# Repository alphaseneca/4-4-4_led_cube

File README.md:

# 4x4x4 LED Cube Project

This repository documents my journey of building a **4x4x4 LED Cube**, including the code, PCB designs, mistakes I made, lessons learned and resources I found along the way. The goal is to use this repository as a **learning journal** and a **reference** for others. This project continues to evolve as I improve the design and explore new features.

<!-- # 4-4-4_led_cube

An interactive 4x4x4 LED Cube project with PCB design, code, debugging logs, and lessons learned, documenting my journey and future improvements.

This project was in the back of my head from few time. I thought this would be a nice showpiece and also enhance my learning and I embarked on this journey of creating an interactive 4x4x4 LED Cube. I hope you enjoy it! -->

## Project Overview

The 4x4x4 LED Cube consists of 64 LEDs arranged in a 3D matrix, controlled using a microcontroller (Arduino in this case). The goal was to create various light patterns by programming the cube and experimenting with animations.

<!--
## Repository Structure

444-LED-Cube/
│
├── Code/ # All code files (Arduino scripts or others)
│ └── main.ino # Example of the main code file
│
├── Images/ # All images related to the project
│ └── build-step1.jpg
│ └── final-cube.jpg
│
├── References/ # Any documentation, schematics, or research material
│ └── schematic.pdf
│ └── useful-links.txt
│
├── Debugging/ # Files describing mistakes, debugging notes
│ └── issues.md
│
└── README.md # Main README with an overview of the project -->

## Repository Structure

- **`images/`**: Photos of the build progress and final results.
- **`4-4-4_led_cube_code/`**: Contains the code for programming the LED cube.
- **`4-4-4_led_cube_pcb/`**: Documentation for all PCB versions.
  - **`v1.0/`**: First version of the PCB, including Gerber files and 3D renderings.
  - **`v2.0/`**: Placeholder for future PCB improvements.
  - **`changelog.md`**: Summarizes changes across PCB iterations.
- **`debugging/`**: Notes on issues encountered and how I solved them.

---

## How to Use the Code

1. Open the PlatformIO IDE and in the **Home** tab , select **Open Project** option then load the **`4-4-4_led_cube_code/`** folder.
2. Select the **`main.cpp`** file in the location **`4-4-4_led_cube_code/src/`** and build it.
3. Connect the microcontroller to the computer using a USB cable.
4. Upload the code and enjoy the light patterns!

---

## The Journey So Far

After seeing a lot of videos on led cube and having the interest to make the room a bit colourful with my own creations, I decided to build a 4x4x4 LED Cube.

Firstly, I gathered the materials and then startred working on the cube itself. The first thing I did was made a frame that could hold the led array so that they will be in the same location. Then started soldering the leds after bending their leads. The next step was to add the array to the frame. And after that the cube was done and after the wiring the 4x4x4 cube was ready.

Creating the PCB for this project was an experience in itself. After completing the cube design, I started working on the PCB. I started with the first version of the PCB with the same design as the original prototype design just to make the wiring more neat and the cube more useable.

This is just the beginning! I plan to continue refining the design, adding new features, and maybe even explore **wireless control** to unlock more creative possibilities.

---

## Debugging Log

- **Issue 1**: The **`Arduino Nano`** did not accepted the code.

  - **Solution**: Tried uploading via ICSP header and failed but found out recently that the bootloader selection was wrong and should have been set to `Old Bootloader`.

- **Issue 2**: The light was strobing a lot.
  - **Solution**: Removed the code that was strobing the leds.

---

## Future Improvements

- **Housing**: Develop an improved housing for the cube.
- **Battery**: Add a battery to the cube to be able to use it without power supply.
- **Add control via webserver**: Add a webserver to control the cube from a web browser.
- **Improved Power Management**: Add decoupling capacitors and better trace design.
- **More Advanced Patterns**: Develop smoother animations and light effects.

---

## References

<!-- - [Link to Notion Page](#)
- Original Schematic: `References/schematic-original.pdf` -->

- [LED Cube Tutorial 1](https://www.youtube.com/watch?v=2BlVUKW5hL0)
- [LED Cube Tutorial 2](https://www.youtube.com/watch?v=YUcU2sJs1o8)

---

<!--
4x4x4 LED Cube Project
This repository documents my journey of building a 4x4x4 LED Cube, including the code, mistakes I made, lessons learned, and resources I found along the way. The purpose of this repository is to serve as a reference for myself and others who are interested in building a similar project or learning from my experience.

Repository Structure
Code/: Contains all the code files used for programming the cube.
Images/: Build progress photos and the final cube images.
References/: Documents, schematics, and useful resources I referred to.
Debugging/: A log of mistakes I made and how I fixed them (or thought I fixed them).

What I Learned
Soldering Practice: This project gave me a lot of practice in precision soldering and reinforced the importance of flux.
Multiplexing and Persistence of Vision (POV): I understood how multiplexing works and how to use it efficiently to control multiple LEDs with fewer pins.
Debugging Complex Wiring: I initially misdiagnosed a wiring issue that caused the LEDs in specific rows to behave incorrectly. It turned out to be a common ground issue, not faulty transistors, as I originally thought. -->

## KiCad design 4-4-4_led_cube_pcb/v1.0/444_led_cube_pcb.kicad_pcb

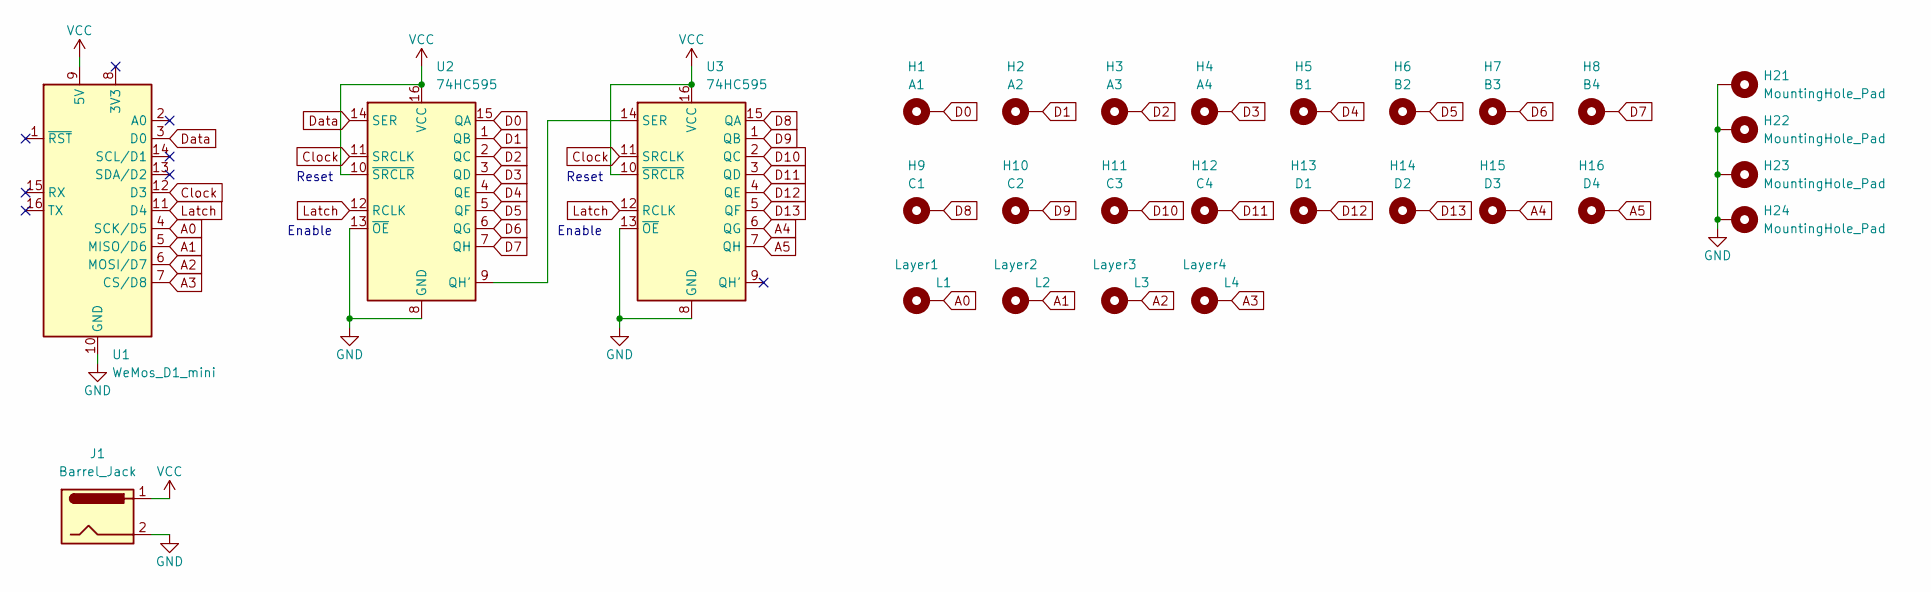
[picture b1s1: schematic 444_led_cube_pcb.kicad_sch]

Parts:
H1: A1; wirebase_footprint
H2: A2; wirebase_footprint
H3: A3; wirebase_footprint
H4: A4; wirebase_footprint
H5: B1; wirebase_footprint
H6: B2; wirebase_footprint
H7: B3; wirebase_footprint
H8: B4; wirebase_footprint
H9: C1; wirebase_footprint
H10: C2; wirebase_footprint
H11: C3; wirebase_footprint
H12: C4; wirebase_footprint
H13: D1; wirebase_footprint
H14: D2; wirebase_footprint
H15: D3; wirebase_footprint
H16: D4; wirebase_footprint
H21, H22, H23, H24: MountingHole_Pad; MountingHole_3mm_Pad_TopBottom
J1: Barrel_Jack; BarrelJack_Horizontal
L1: Layer1; wirebase_footprint
L2: Layer2; wirebase_footprint
L3: Layer3; wirebase_footprint
L4: Layer4; wirebase_footprint
U1: WeMos_D1_mini; WEMOS_D1_mini_light
U2, U3: 74HC595; DIP-16_W7.62mm

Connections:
A0: L1.1, U1.4 (SCK/D5)
A1: L2.1, U1.5 (MISO/D6)
A2: L3.1, U1.6 (MOSI/D7)
A3: L4.1, U1.7 (CS/D8)
A4: H15.1, U3.6 (QG)
A5: H16.1, U3.7 (QH)
Clock: U1.12 (D3), U2.11 (SRCLK), U3.11 (SRCLK)
D0: H1.1, U2.15 (QA)
D1: H2.1, U2.1 (QB)
D2: H3.1, U2.2 (QC)
D3: H4.1, U2.3 (QD)
D4: H5.1, U2.4 (QE)
D5: H6.1, U2.5 (QF)
D6: H7.1, U2.6 (QG)
D7: H8.1, U2.7 (QH)
D8: H9.1, U3.15 (QA)
D9: H10.1, U3.1 (QB)
D10: H11.1, U3.2 (QC)
D11: H12.1, U3.3 (QD)
D12: H13.1, U3.4 (QE)
D13: H14.1, U3.5 (QF)
Data: U1.3 (D0), U2.14 (SER)
GND: H21.1, H22.1, H23.1, H24.1, J1.2, U1.10 (GND), U2.8 (GND), U2.13 (~OE), U3.8 (GND), U3.13 (~OE)
Latch: U1.11 (D4), U2.12 (RCLK), U3.12 (RCLK)
unnamed: U2.9 (QH'), U3.14 (SER)
VCC: J1.1, U1.9 (5V), U2.10 (~SRCLR), U2.16 (VCC), U3.10 (~SRCLR), U3.16 (VCC)

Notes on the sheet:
Reset
Enable

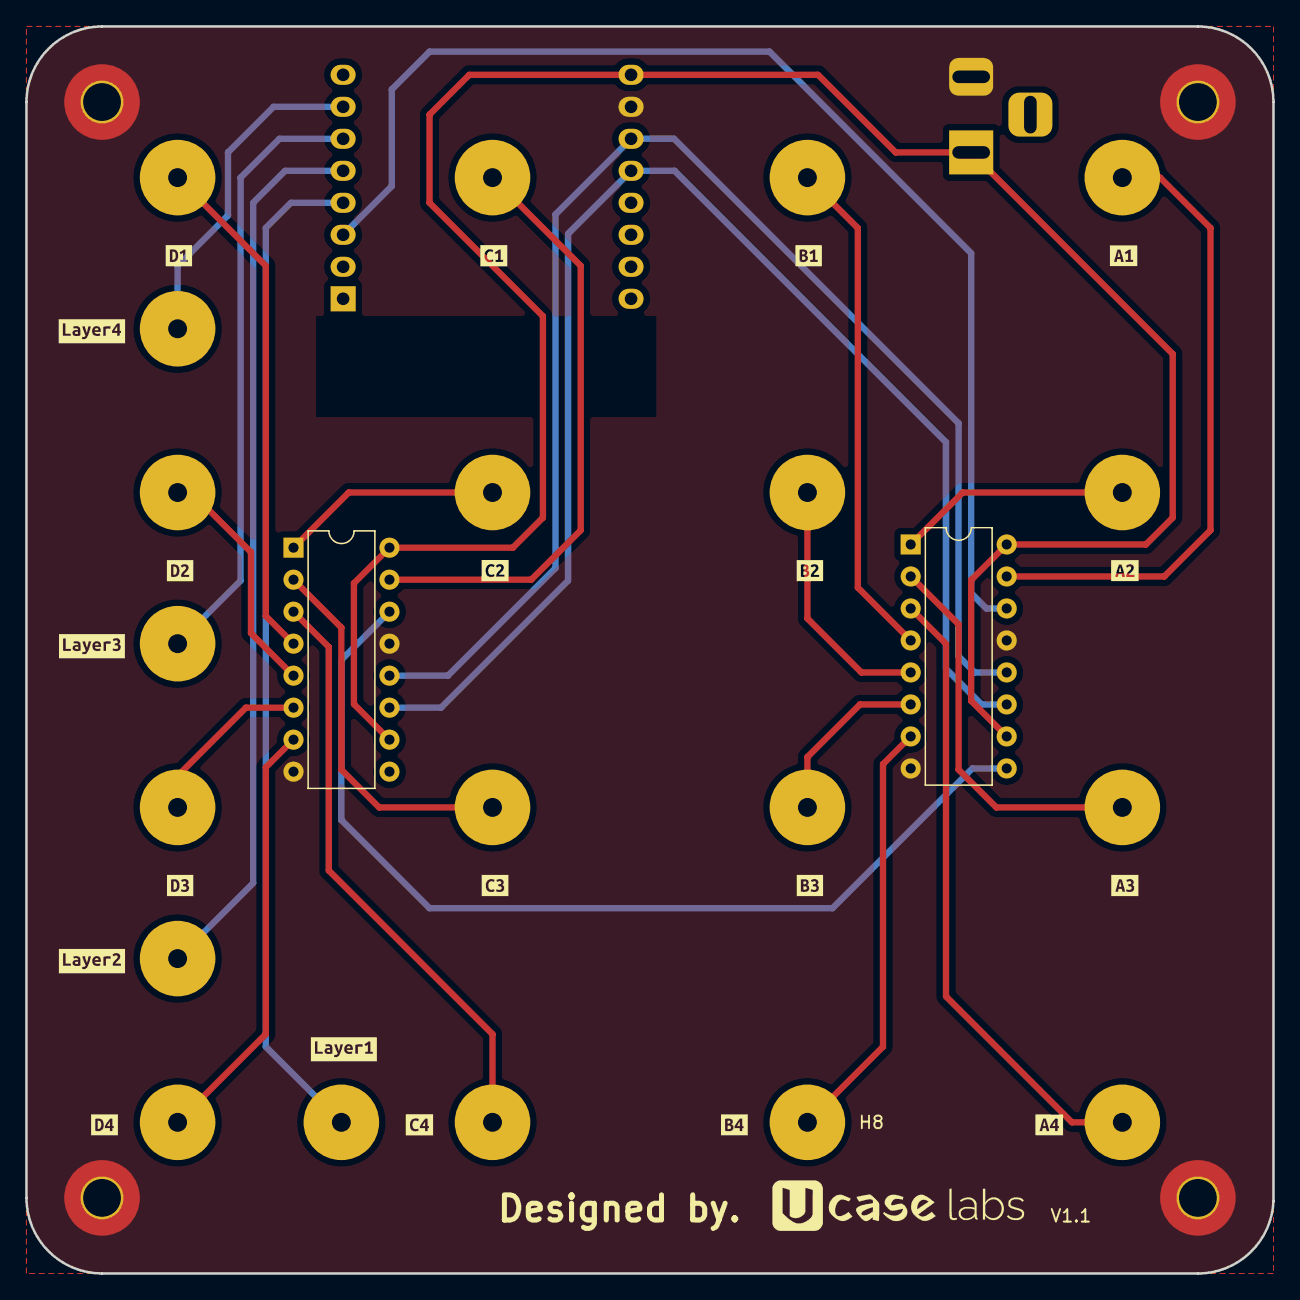
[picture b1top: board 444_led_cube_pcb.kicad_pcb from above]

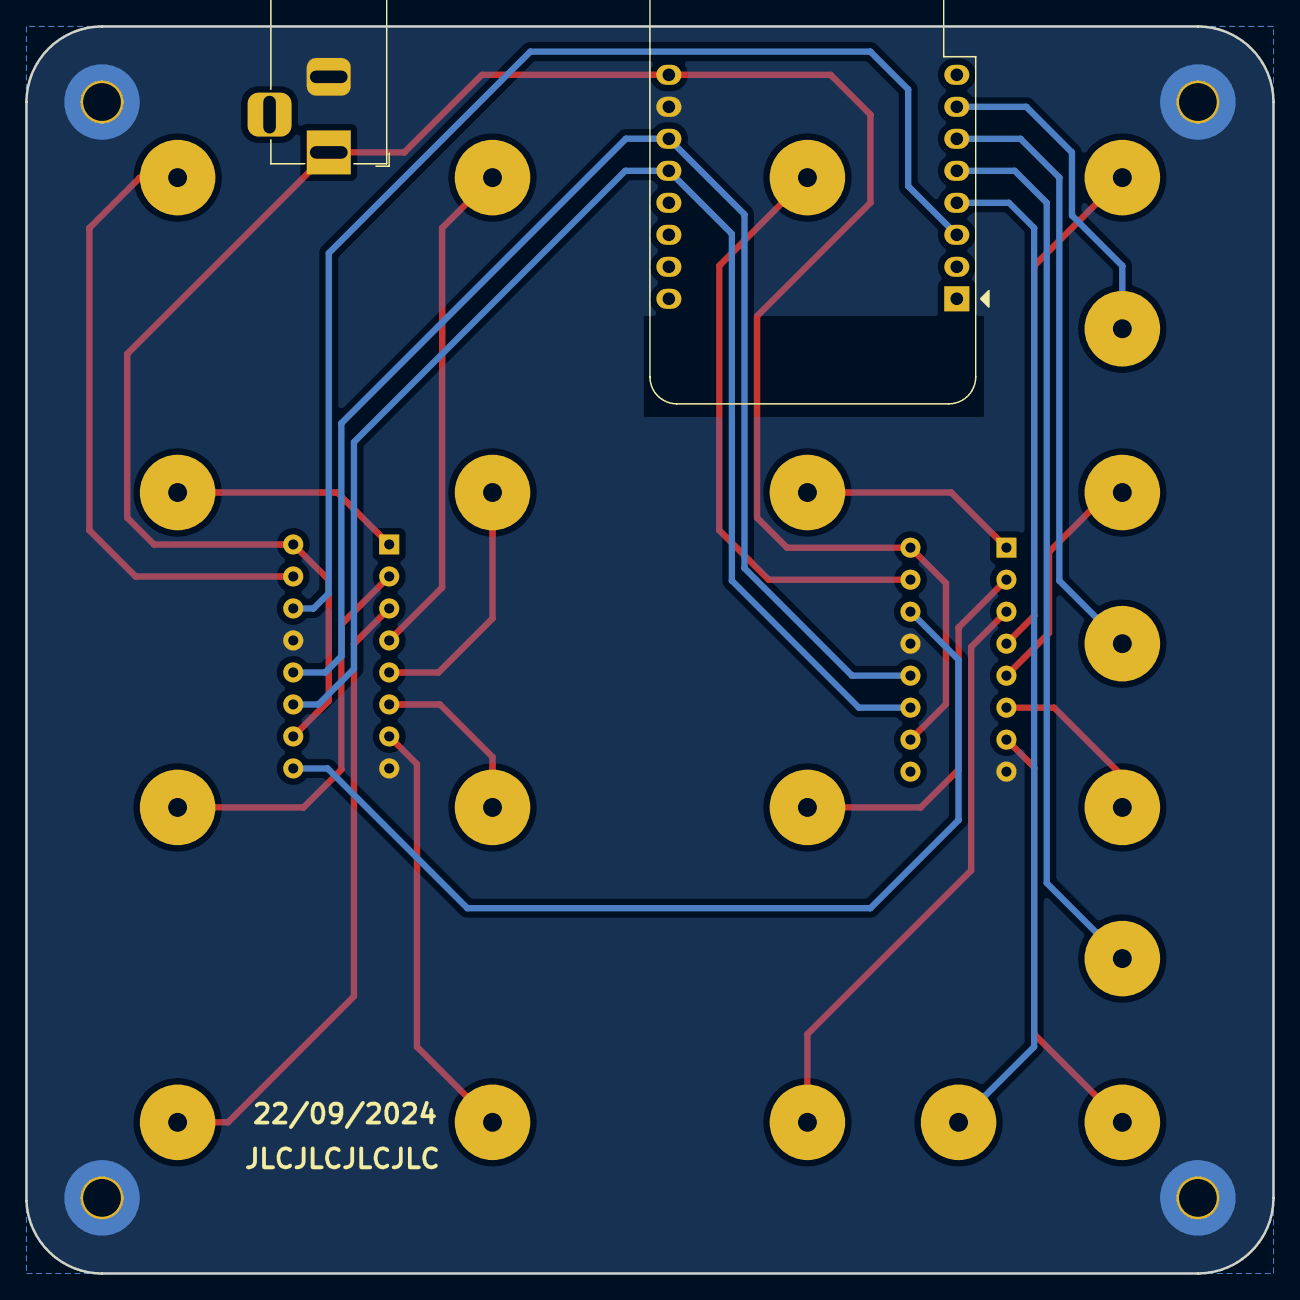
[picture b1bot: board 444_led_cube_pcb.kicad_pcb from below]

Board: 2 copper layers, 99.0 x 99.0 mm, 48 parts (2 on the bottom side), 26 nets.

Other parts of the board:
kibuzzard-6643D9ED: G***; kibuzzard-6643D9ED
kibuzzard-6643D9FF: G***; kibuzzard-6643D9FF
kibuzzard-6643DA1F: G***; kibuzzard-6643DA1F
kibuzzard-6643DA2D: G***; kibuzzard-6643DA2D
kibuzzard-6643DAD8: G***; kibuzzard-6643DAD8
kibuzzard-6643DAE2: G***; kibuzzard-6643DAE2
kibuzzard-6643DB1C: G***; kibuzzard-6643DB1C
kibuzzard-6643DB4E: G***; kibuzzard-6643DB4E
kibuzzard-6643DB5E: G***; kibuzzard-6643DB5E
kibuzzard-6643DB07: G***; kibuzzard-6643DB07
kibuzzard-6643DB44: G***; kibuzzard-6643DB44
kibuzzard-6643DBBB: G***; kibuzzard-6643DBBB
kibuzzard-6643DBC3: G***; kibuzzard-6643DBC3
kibuzzard-6643DBCA: G***; kibuzzard-6643DBCA
kibuzzard-6643DBD4: G***; kibuzzard-6643DBD4
kibuzzard-6643DBDA: G***; kibuzzard-6643DBDA
kibuzzard-6643DBE0: G***; kibuzzard-6643DBE0
kibuzzard-6643DBE7: G***; kibuzzard-6643DBE7
kibuzzard-6643DBED: G***; kibuzzard-6643DBED
kibuzzard-6643DBF5: G***; kibuzzard-6643DBF5

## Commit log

2024-10-19 added images and finalized the readme file
2024-10-19 added the image tags and finalized
2024-10-19 changed the image size
2024-10-19 added the code and the pcb files
2024-10-25 added gitignore file and fixed the typo
2025-01-27 changed the enviromnent to d1 mini
2025-01-27 changed the code for newer version
